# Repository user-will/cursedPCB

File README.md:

# Cursed PCB

Cursed PCB is a programmable light board with an ATtiny412 microcontroller, four individually addressable RGB LEDs, onboard USB-C power, and an onboard CH340 SerialUPDI programmer. Plug it into a computer, install the ATtiny board support in Arduino IDE, and upload your own light patterns.

> **Quick links:** [LED example](examples/LED_example/LED_example.ino) · [printable quick-start guide](docs/cursed-pcb-quick-start.pdf) · [nine-card Letter sheet](docs/cursed-pcb-card-sheet-letter-3x3.pdf) · [single 70 × 90 mm card](docs/cursed-pcb-setup-card-70x90mm.pdf) · [megaTinyCore documentation](https://github.com/SpenceKonde/megaTinyCore)

## Repository contents

- [`examples/LED_example/LED_example.ino`](examples/LED_example/LED_example.ino) — ready-to-upload LED animations and optional button support
- [`docs/cursed-pcb-quick-start.pdf`](docs/cursed-pcb-quick-start.pdf) — printable two-page quick-start guide
- [`docs/cursed-pcb-card-sheet-letter-3x3.pdf`](docs/cursed-pcb-card-sheet-letter-3x3.pdf) — nine 70 × 90 mm cards arranged 3 × 3 on US Letter paper
- [`docs/cursed-pcb-setup-card-70x90mm.pdf`](docs/cursed-pcb-setup-card-70x90mm.pdf) — one 70 × 90 mm setup card
- [`attiny412_addressable.kicad_sch`](attiny412_addressable.kicad_sch) — KiCad schematic
- [`attiny412_addressable.kicad_pcb`](attiny412_addressable.kicad_pcb) — KiCad PCB layout
- [`attiny412_addressable.kicad_pro`](attiny412_addressable.kicad_pro) — KiCad project settings

## Printing the setup cards

Use the [nine-card Letter sheet](docs/cursed-pcb-card-sheet-letter-3x3.pdf) to print nine cards on one single-sided sheet of US Letter paper or cardstock. Each finished card is 70 × 90 mm.

In the print dialog, select **Letter**, **Portrait**, **Actual size** or **100% scale**, and one-sided printing. Do not select “Fit to page.” Use the small corner marks to align your cuts.

## What you need

- The Cursed PCB
- A USB-C **data** cable (some charging-only cables cannot upload code)
- [Arduino IDE](https://www.arduino.cc/en/software)
- The `LED_example` sketch in this repository

No separate LED library download is required. The `tinyNeoPixel_Static` library used by the example is included with megaTinyCore.

## 1. Install ATtiny412 support

The ATtiny412 is not included in Arduino IDE by default. Install the **megaTinyCore** board package:

1. Open Arduino IDE.
2. Open **File → Preferences**. On macOS, open **Arduino IDE → Settings**.
3. Add this URL to **Additional Boards Manager URLs**:

   ```text
   http://drazzy.com/package_drazzy.com_index.json
   ```

   If another URL is already present, use the button beside the field and add this URL on a new line.

4. Open **Tools → Board → Boards Manager**.
5. Search for `megaTinyCore`.
6. Install the newest version of **megaTinyCore by Spence Konde**.

The package includes the compiler, upload utility, and `tinyNeoPixel` libraries needed by this board.

## 2. Connect and configure the board

Connect the board directly to the computer with a USB-C data cable. The power LED should turn on and a new serial port should appear in Arduino IDE.

Select these settings under **Tools**:

| Setting | Selection |
| --- | --- |
| Board | **megaTinyCore → ATtiny412/402/212/202** |
| Clock | **20 MHz internal** |
| BOD Voltage Level | **4.2V (20 MHz or less)** |
| millis()/micros() Timer | **Enabled (default timer)** |
| Programmer | **SerialUPDI - 230400 baud** |

Choose the board entry **without** “w/Optiboot.” This board programs the ATtiny412 directly over UPDI and does not need a bootloader.

The onboard CH340 connection is dedicated to UPDI programming. It is not connected to the ATtiny412's normal UART pins, so Arduino Serial Monitor will not display `Serial.print()` output through this USB-C connection. PA6/TX and PA7/RX remain available on the six-pin header for an external serial adapter.

## 3. Open and upload the example

1. Download or clone this repository.
2. Open [`examples/LED_example/LED_example.ino`](examples/LED_example/LED_example.ino) in Arduino IDE.
3. Compile with **Sketch → Verify/Compile**.
4. Upload with **Sketch → Upload Using Programmer**. The regular Upload button is not used for this UPDI setup.

After the upload finishes, the four LEDs run through red, green, blue, white, a rainbow sweep, and a moving white chase.

### Optional mode button

The example supports an optional normally-open pushbutton connected between exposed pins **0 (PA6)** and **2 (PA1)**. No external resistor is needed for this example: the sketch drives PA6 low and enables PA1's internal pull-up. Each press advances to the next animation.

If no button is connected, the example still works. It automatically shows the four solid colors and then continues with the rainbow sweep.

## Programming the lights

The four onboard LEDs are SK6812MINI-E addressable RGB LEDs connected as one chain. The first LED's data input is connected to **PA3**, which megaTinyCore calls Arduino pin **4**.

The important setup from the example is:

```cpp
#include <tinyNeoPixel_Static.h>

constexpr uint8_t LED_PIN = PIN_PA3;  // Arduino pin 4
constexpr uint8_t NUM_LEDS = 4;

byte pixelData[NUM_LEDS * 3];
tinyNeoPixel leds(NUM_LEDS, LED_PIN, NEO_GRB, pixelData);

void setup() {
  pinMode(LED_PIN, OUTPUT);
  leds.setBrightness(20);              // 0 to 255
  leds.setPixelColor(0, 255, 0, 0);   // first LED: red
  leds.show();
}
```

`tinyNeoPixel_Static` keeps the LED buffer in a fixed array, which is helpful on the ATtiny412's limited memory. Set colors with `setPixelColor()`, then call `show()` to send the updated buffer to the LEDs. The LEDs use `NEO_GRB` byte order.

Keep the brightness modest while experimenting. Four LEDs at full white use much more current and can be uncomfortably bright.

## Pinout

With the component side facing up and the USB-C connector at the bottom, the six-pin header reads left to right:

| Header label | Arduino pin | ATtiny412 pin | Common functions |
| --- | ---: | --- | --- |
| 5V | — | VDD | Regulated 5 V rail/output — **not an external power input** |
| GND | — | GND | Ground |
| 0 | 0 | PA6 | Digital I/O, DAC, UART TX |
| 1 | 1 | PA7 | Digital I/O, UART RX |
| 2 | 2 | PA1 | Digital I/O, I²C SDA |
| 3 | 3 | PA2 | Digital I/O, I²C SCL |

Arduino pin **4 / PA3** controls the onboard LEDs and is not on the six-pin header. **PA0 / UPDI** is reserved for programming.

The separate three-pin header is labeled **UPDI, GND, VCC** from top to bottom when the USB-C connector is at the bottom. For standalone external power, connect the supply's positive lead to **VCC** and its negative lead to **GND**. VCC feeds the onboard voltage regulator. **UPDI** is for advanced external programming; none of these pins are needed for normal USB-C programming.

## Power and handling

- For normal use, power and program the board through USB-C.
- For standalone external power, connect the supply to **VCC** and **GND** on the side three-pin header. **Do not power the board through the 5V pin.**
- VCC passes through an onboard **L78L05 linear regulator**. It produces a fixed 5 V rail and is rated for a maximum of **100 mA total output current**. The board itself and all four LEDs share that limit.
- The regulator needs approximately **7 V or more at VCC** to maintain a regulated 5 V output. Keep VCC at or below the **recommended 20 V maximum**. The regulator IC's 30 V rating is an absolute maximum, not a recommended operating voltage. Higher input voltage creates more heat and reduces the practical current available.
- Regulator heat is approximately `(VCC input − 5 V) × current`. Keep external supply voltage and LED brightness as low as practical. Four LEDs at high or full-white brightness can exceed the regulator's 100 mA rating.
- Never connect an external supply to VCC while USB-C is connected. The two power sources are not isolated.
- The exposed **5V** header pin is the regulator's output/board rail. It may be used only as a limited 5 V output when the board is properly powered; never feed an external supply into it.
- The board has exposed electronics. Prevent metal objects, conductive surfaces, and loose wires from shorting it.
- Disconnect power before changing wiring. Observe polarity when using external power.
- The LEDs can be very bright. Avoid staring directly at them at high brightness.

## Troubleshooting

### No serial port appears

- Try a known USB-C data cable and another USB port.
- Disconnect and reconnect the board while watching **Tools → Port**.
- If the computer does not recognize the onboard CH340 USB serial device, install the CH340 driver for your operating system.

### Upload fails or reports “UPDI initialization failed”

- Confirm **ATtiny412/402/212/202** (without Optiboot), **BOD Voltage Level → 4.2V**, and **SerialUPDI - 230400 baud** are selected.
- Use **Sketch → Upload Using Programmer**, not the regular Upload command.
- Close any serial monitor or other application using the board's port.
- Try **SerialUPDI - SLOW: 57600 baud** under **Tools → Programmer**.
- Unplug the board, reconnect it, reselect the port, and try again.

### The sketch uploads but the LEDs stay dark

- Confirm the sketch uses four pixels, `NEO_GRB`, and LED pin `PIN_PA3` or Arduino pin `4`.
- Make sure the LED data pin is configured as `OUTPUT` when using `tinyNeoPixel_Static`.
- Increase `setBrightness(20)` slightly while testing, but do not start at full brightness.

### The sketch is too large

The ATtiny412 has 4 KB of program flash and 256 bytes of SRAM. Prefer `tinyNeoPixel_Static`, avoid large strings and unnecessary libraries, and keep the pixel buffer at `4 × 3 = 12` bytes.

## Hardware summary

- ATtiny412, 4 KB flash / 256 bytes SRAM
- Four SK6812MINI-E addressable RGB LEDs
- USB-C connector with onboard CH340 SerialUPDI programming
- Side VCC external-power input through an L78L05 regulator: recommended 20 V maximum input, fixed 5 V output, 100 mA maximum total output
- Four exposed GPIO pins, including I²C SDA/SCL
- Approximately 58 mm × 29.5 mm
- Four 2.2 mm mounting holes

For deeper ATtiny and library information, see the official [megaTinyCore installation guide](https://github.com/SpenceKonde/megaTinyCore/blob/master/Installation.md), [megaTinyCore reference](https://github.com/SpenceKonde/megaTinyCore), and [tinyNeoPixel reference](https://github.com/SpenceKonde/megaTinyCore/blob/master/megaavr/extras/tinyNeoPixel.md).

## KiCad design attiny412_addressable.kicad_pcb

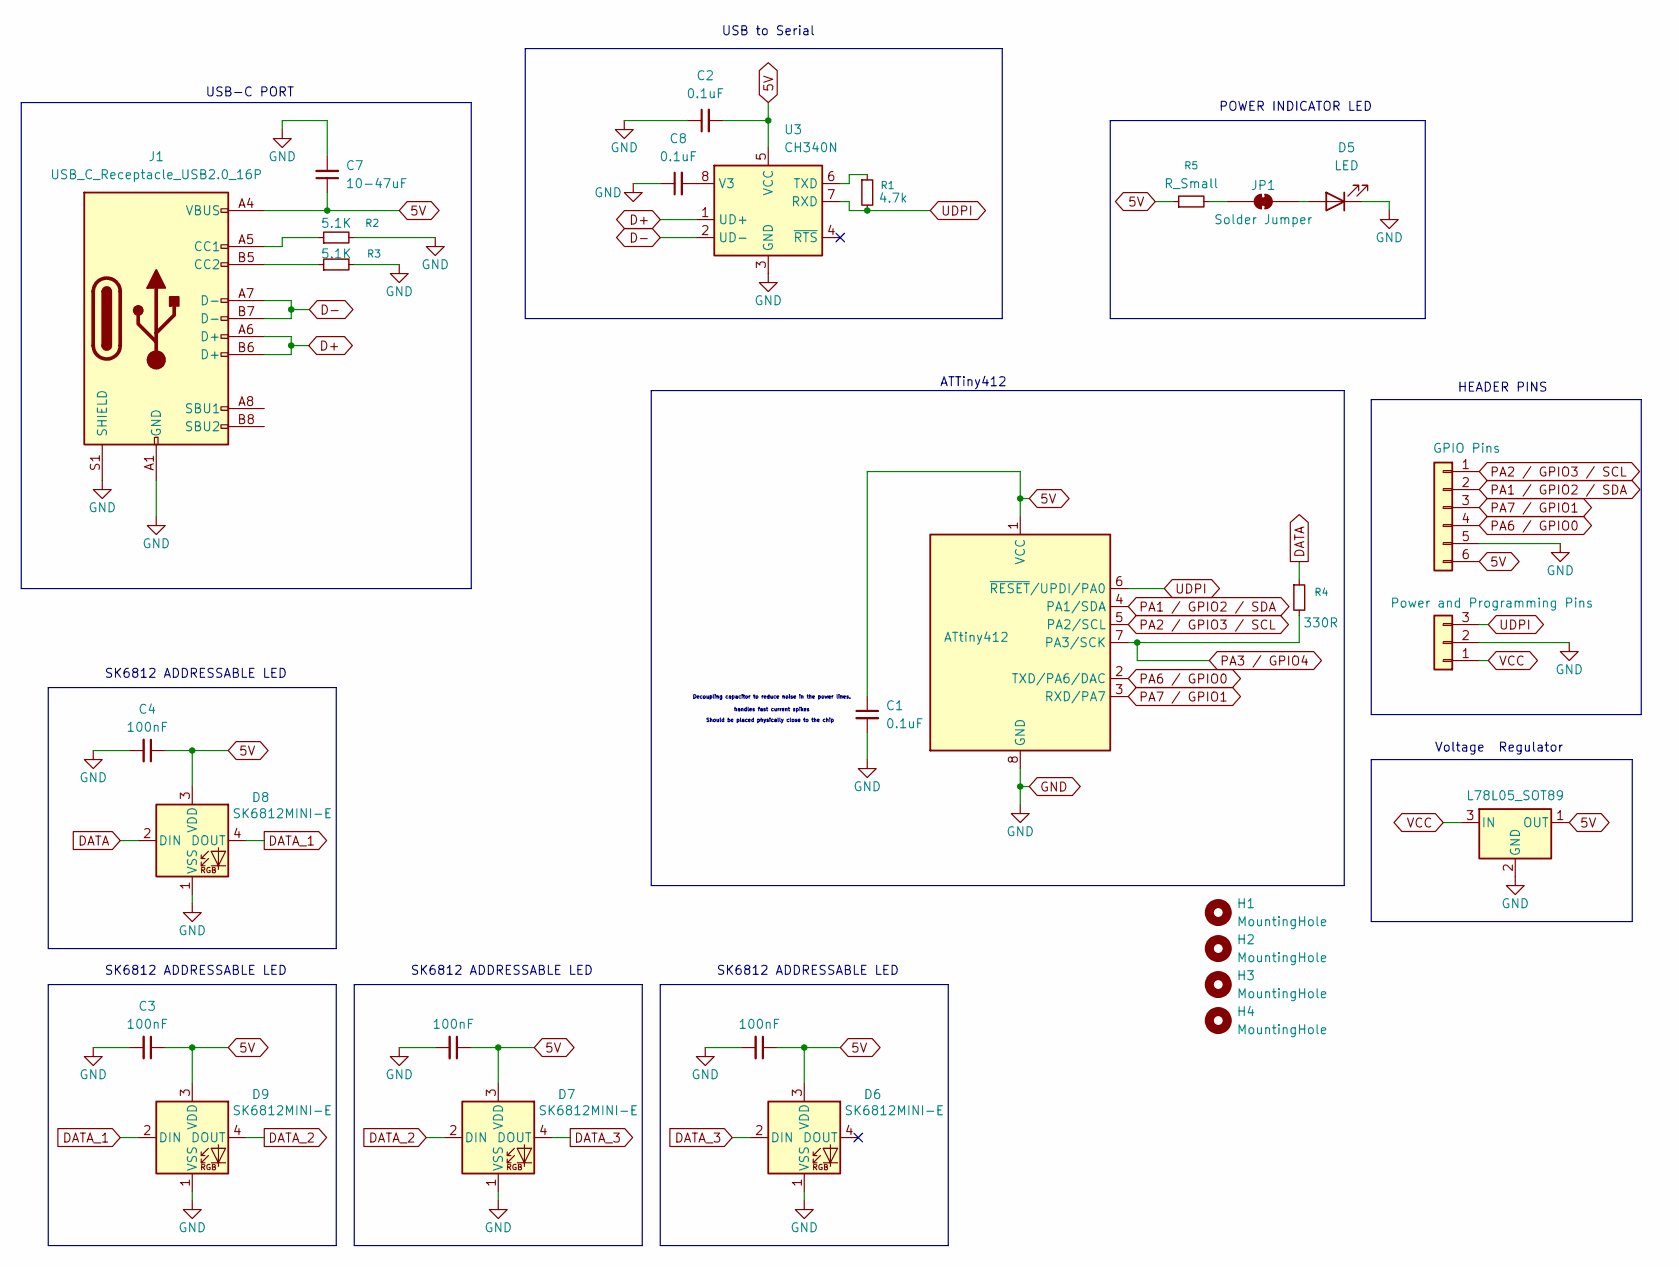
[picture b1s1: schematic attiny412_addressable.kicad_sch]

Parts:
C1: 0.1uF_0603_16V; C_0805_2012Metric_Pad1.18x1.45mm_HandSolder; Part Number 0603YC104KAT2A; JLCPCB ID C14663
C2, C8: 0.1uF; C_0805_2012Metric_Pad1.18x1.45mm_HandSolder
C3, C4, C5, C6: 100nF; C_0805_2012Metric_Pad1.18x1.45mm_HandSolder
C7: 10-47uF; C_0805_2012Metric_Pad1.18x1.45mm_HandSolder
D5: LED; LED_0805_2012Metric_Pad1.15x1.40mm_HandSolder
D6, D7, D8, D9: SK6812MINI-E; LED_SK6812MINI-E_3.2x2.8mm_P1.5mm_ReverseMount
H1, H2, H3, H4: MountingHole; MountingHole_2.2mm_M2
J1: USB_C_Receptacle_USB2.0_16P; USB_C_Receptacle_Palconn_UTC16-G
J2: GPIO Pins; PinHeader_1x06_P2.54mm_Vertical
J3: Power and Programming Pins; PinHeader_1x03_P2.54mm_Vertical
JP1: Solder Jumper; SolderJumper-2_P1.3mm_Bridged_RoundedPad1.0x1.5mm
R1: 4.7k; R_0805_2012Metric_Pad1.20x1.40mm_HandSolder
R2, R3: 5.1K; R_0805_2012Metric_Pad1.20x1.40mm_HandSolder
R4: 330R; R_0805_2012Metric_Pad1.20x1.40mm_HandSolder
R5: R_Small; R_0805_2012Metric_Pad1.20x1.40mm_HandSolder
U1: ATtiny412; SOIC-8_5.3x5.3mm_P1.27mm
U2: L78L05_SOT89; SOT-89-3_Handsoldering
U3: CH340N; JEITA_SOIC-8_3.9x4.9mm_P1.27mm

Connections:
5V: C1.1, C2.2, C3.1, C4.1, C5.1, C6.1, C7.1, D6.3 (VDD), D7.3 (VDD), D8.3 (VDD), D9.3 (VDD), J1.A4 (VBUS), J1.A9 (VBUS), J1.B4 (VBUS), J1.B9 (VBUS), J2.6, R5.1, U1.1 (VCC), U2.1 (OUT), U3.5 (VCC)
D+: J1.A6 (D+), J1.B6 (D+), U3.1 (UD+)
D-: J1.A7 (D-), J1.B7 (D-), U3.2 (UD-)
DATA: D8.2 (DIN), R4.1
DATA_1: D8.4 (DOUT), D9.2 (DIN)
DATA_2: D7.2 (DIN), D9.4 (DOUT)
DATA_3: D6.2 (DIN), D7.4 (DOUT)
GND: C1.2, C2.1, C3.2, C4.2, C5.2, C6.2, C7.2, C8.1, D5.1 (K), D6.1 (VSS), D7.1 (VSS), D8.1 (VSS), D9.1 (VSS), J1.A1 (GND), J1.A12 (GND), J1.B1 (GND), J1.B12 (GND), J1.S1 (SHIELD), J2.5, J3.2, R2.2, R3.2, U1.8 (GND), U2.2 (GND), U3.3 (GND)
unnamed: D5.2 (A), JP1.2 (B)
unnamed: J1.A5 (CC1), R2.1
unnamed: J1.B5 (CC2), R3.1
unnamed: JP1.1 (A), R5.2
unnamed: R1.1, U3.6 (TXD)
unnamed: C8.2, U3.8 (V3)
PA1 / GPIO2 / SDA: J2.2, U1.4 (PA1/SDA)
PA2 / GPIO3 / SCL: J2.1, U1.5 (PA2/SCL)
PA3 / GPIO4: R4.2, U1.7 (PA3/SCK)
PA6 / GPIO0: J2.4, U1.2 (TXD/PA6/DAC)
PA7 / GPIO1: J2.3, U1.3 (RXD/PA7)
UDPI: J3.3, R1.2, U1.6 (~RESET/UPDI/PA0), U3.7 (RXD)
VCC: J3.1, U2.3 (IN)

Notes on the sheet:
handles fast current spikes
SK6812 ADDRESSABLE LED
HEADER PINS
Should be placed physically close to the chip
USB to Serial
ATTiny412
POWER INDICATOR LED
USB-C PORT
Voltage Regulator
Decoupling capacitor to reduce noise in the power lines.

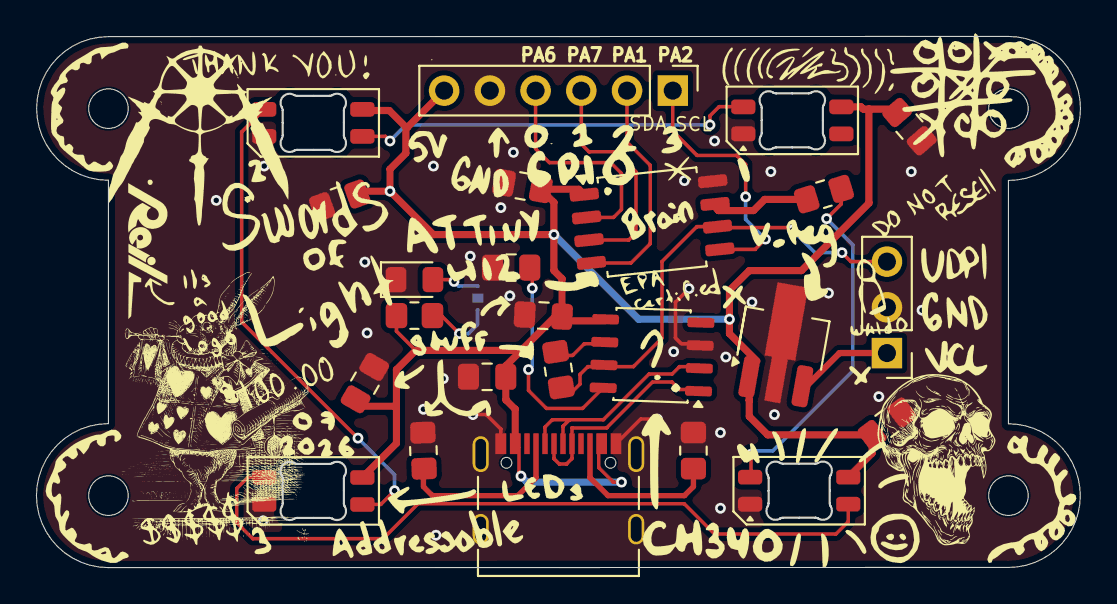
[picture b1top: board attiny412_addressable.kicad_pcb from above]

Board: 2 copper layers, 58.0 x 29.5 mm, 29 parts (1 on the bottom side), 21 nets.
